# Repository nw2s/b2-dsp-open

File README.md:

# b2-dsp-open
Open sourced hardware and software for the b2-dsp module

## Important Links

[nw2s website](http://nw2s.net)

[nw2s::b2/dsp Confluence](https://nw2sdevices.atlassian.net/wiki/display/NW2SB2DSP)

[nw2s::b2/dsp Jira](https://nw2sdevices.atlassian.net/secure/RapidBoard.jspa?rapidView=2&projectKey=B2)

[nw2s::b2/dsp open source repository](https://github.com/nw2s/b2-dsp-open)

[nw2s on facebook](https://www.facebook.com/nw2smodular/)

## Status

[19-Nov-2016]
A good portion of the hardware design is complete. The panel design is complete and most of the conponent selection is done. The panel board has a little bit of work with regards to spacing and vertical alignment, but is otherwise complete. The mainboard still has a bit of layout work to do to be able to fit everything in with a minimum of interference. There is still a decent amount of work there and prototyping to do. 

Software-wise, I'm primarily working through some issue with the AM57x with the TI Linux kernel and access to the DSP chips via OpenCL. Much of the controller/worker architecture is completed and there is support for a wide array of USB devices. I'm actively building out playable patches for some specific devices. 

[You can see what I'm probably working on in Jira](https://nw2sdevices.atlassian.net/secure/RapidBoard.jspa?rapidView=2&projectKey=B2). Since this is a very small team, it doesn't get updated as often as it shoudld, but it will give you an idea of some of the recent accomplishments and near-future goals. If you aren't familiar with a Kanban board, that is technically how I'm working through the tasks. 

## Licensing
The nw2s::b2/dsp is an open source project. Both the hardware and the software are released as open-source. 

This project builds on many contributors and is open source so that I can give back to the community. Most of them are unknowing contributors, so I've attempted to give credit wherever possible. Code, samples, algorithms, ideas: many of them are gleaned or borrowed, others are built upon. Still others are completely original. 

In the spirit of open-source, I ask that any use of these materials be properly credited and used in accordance with the applicable licenses. If you are not familiar with the common terms of open-source, I ask that you do a little research. Different parts of the project are licensed differently, depending on what it is. 

For the most part, all nw2s::b2/dsp code is licensed with GPL v3. GPL is a restrictive open source license. The gist is that you have access to the code for your own use. You may modify the source code, but you must release the modified source code. GPL also requires that all code that links to the nw2s::b2/dsp code must also be released as open source. This means that if you use any of this code in a project, your project must also be open source. 

With a few exceptions, the documentation and reference materials have been released as Creative Commons Attribution Share Alike. This means that you're free to create new works based on this documentation as long as you give attribution and also share the source material. 

The hardware is open-sourced as well. This is important. There are not many truly open-source hardware projects out there. All of the hardware design is my own and I am sharing it with the community. The hardware is licensed via the CERN OHL v1.2. This means that you are free to modify and even sell derivative works, however all source materials must remain open-sourced as well under the same license. Unfortunately due to the type of project, these are not trivial to source nor trivial to build. Fortunately for you, I don't really make that much money on them.

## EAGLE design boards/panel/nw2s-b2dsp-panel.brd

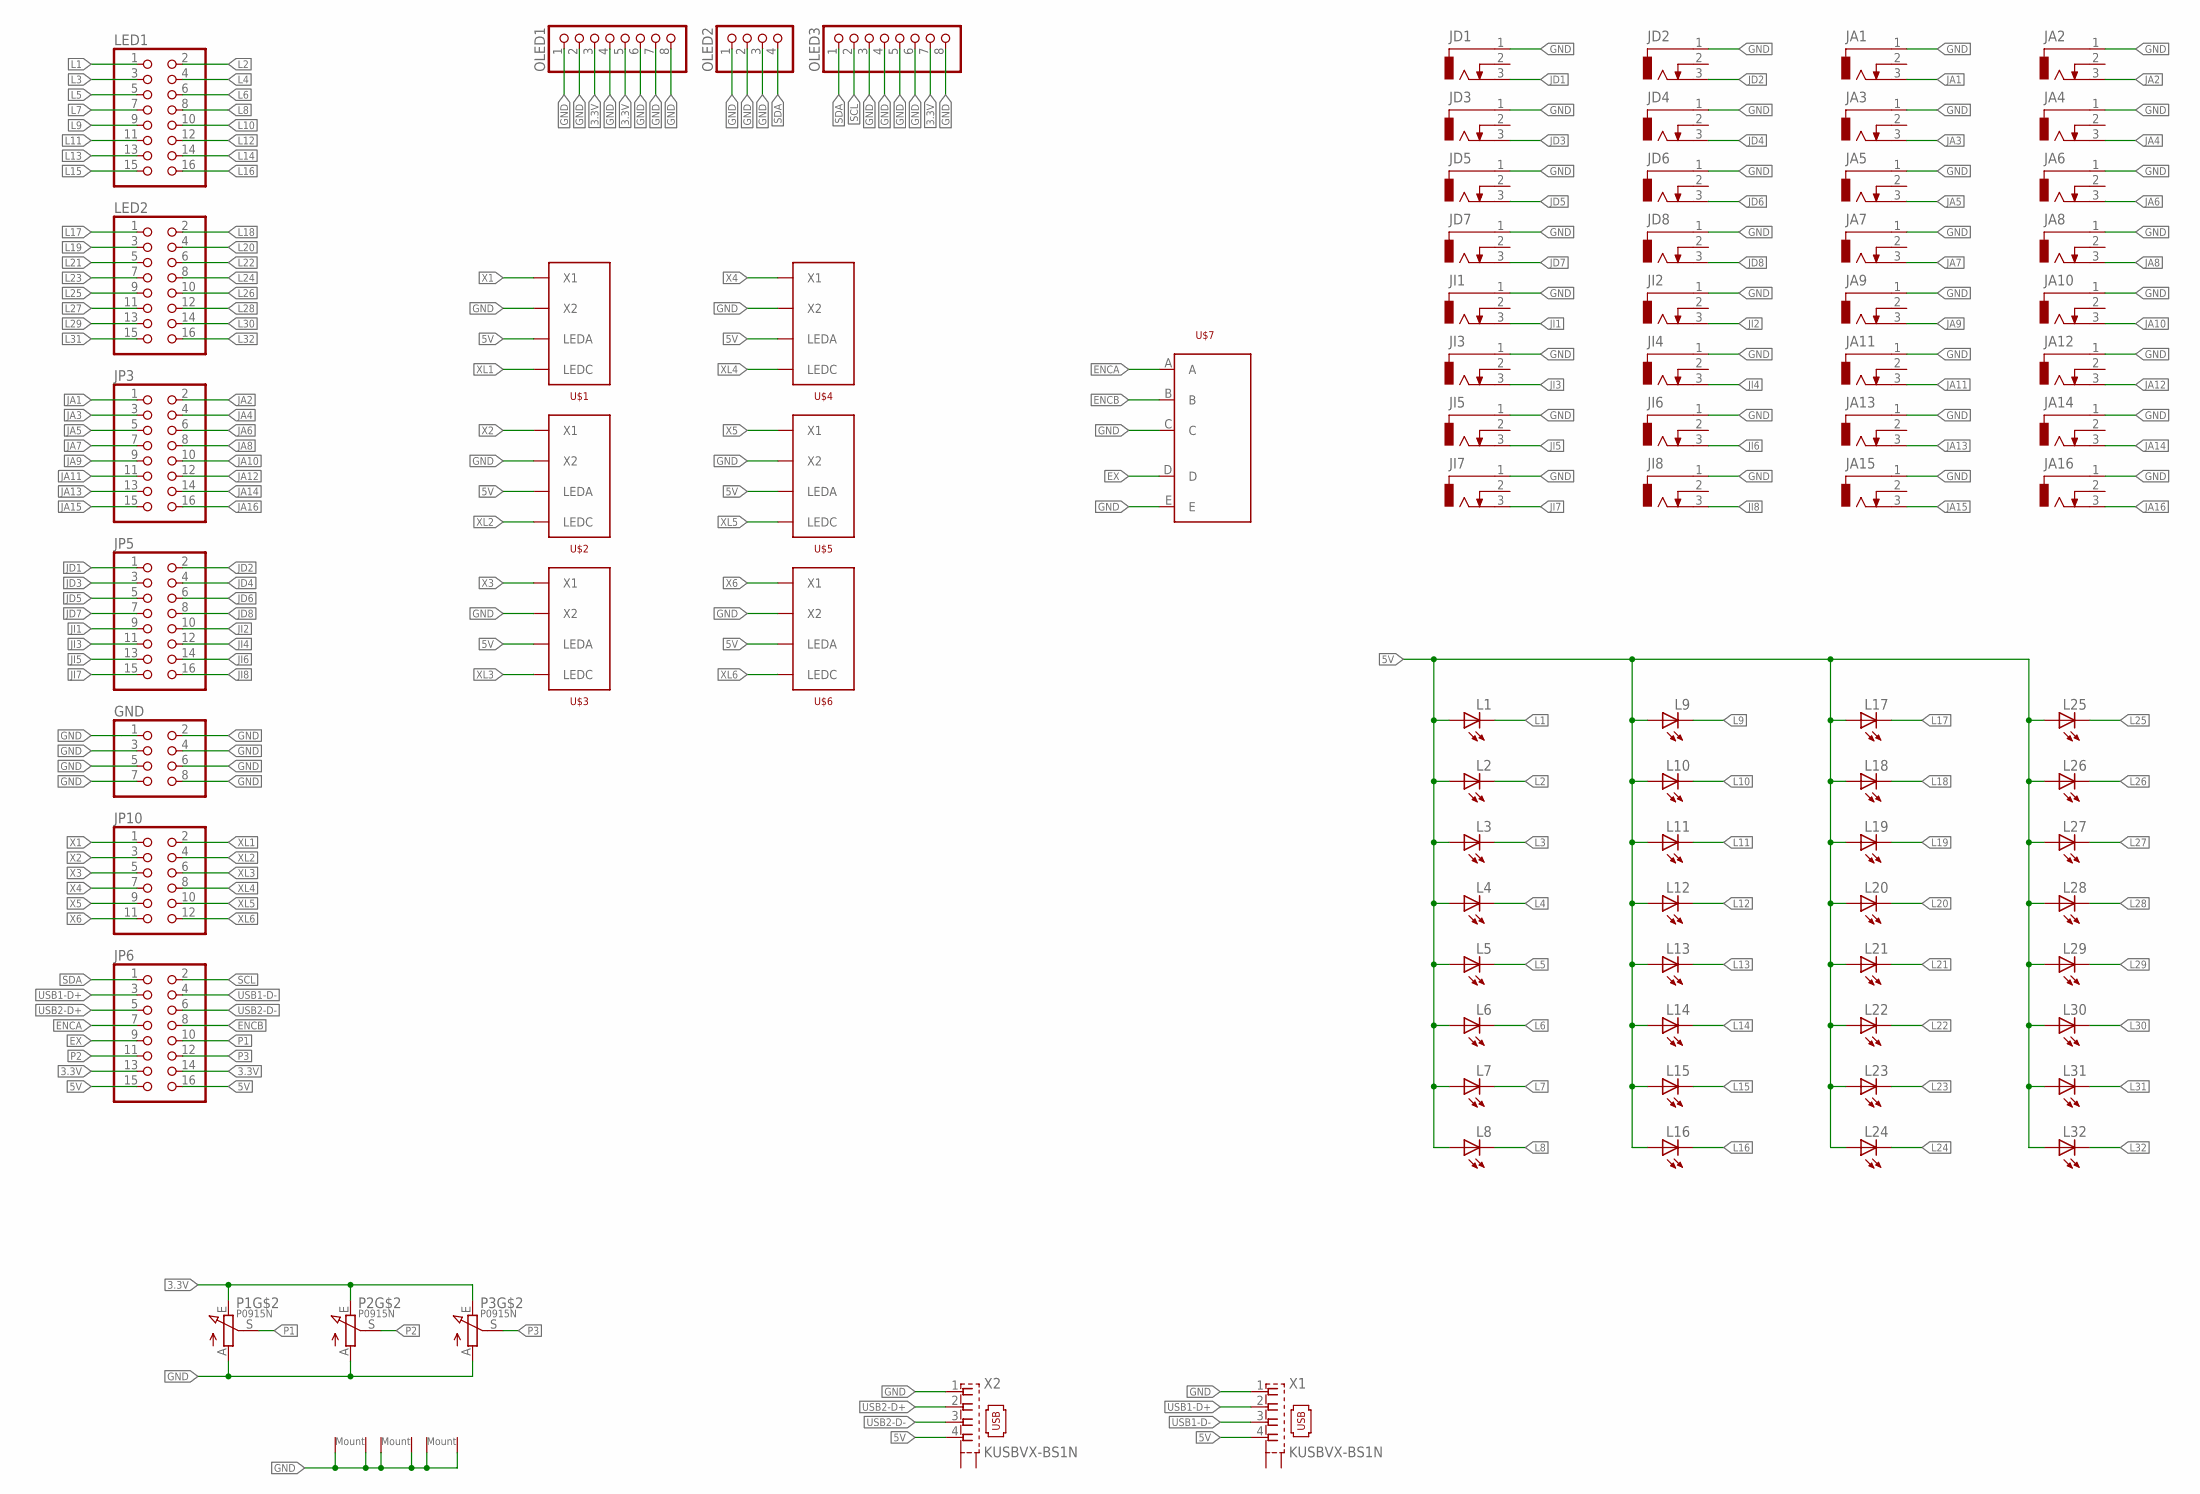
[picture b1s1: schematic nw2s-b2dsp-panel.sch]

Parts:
GND: PINHD-2X4; 2X04
JA1, JA2, JA3, JA4, JA5, JA6, JA7, JA8, JA9, JA10, JA11, JA12, JA13, JA14, JA15, JA16: THONK35A2; THONK35A-2
JD1, JD2, JD3, JD4, JD5, JD6, JD7, JD8: THONK35A2; THONK35A-2
JI1, JI2, JI3, JI4, JI5, JI6, JI7, JI8: THONK35A2; THONK35A-2
JP3, JP5, JP6: PINHD-2X8; 2X08
JP10: PINHD-2X6; 2X06
L1, L2, L3, L4, L5, L6, L7, L8, L9, L10, L11, L12, L13, L14, L15, L16, L17, L18, L19, L20, L21, L22, L23, L24, L25, L26, L27, L28, L29, L30, L31, L32: LED3MM
LED1, LED2: PINHD-2X8; 2X08
OLED1, OLED3: PINHD-1X8; 1X08
OLED2: PINHD-1X4; 1X04
P1, P2, P3: P0915N
U$1, U$2, U$3, U$4, U$5, U$6: MEC5G
U$7: EN11X; EN11
X1, X2: KUSBVX-BS1N

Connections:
3.3V: JP6.13, JP6.14, OLED1.3, OLED1.5, OLED3.7, P1.E, P2.E, P3.E
5V: JP6.15, JP6.16, L1.A, L2.A, L3.A, L4.A, L5.A, L6.A, L7.A, L8.A, L9.A, L10.A, L11.A, L12.A, L13.A, L14.A, L15.A, L16.A, L17.A, L18.A, L19.A, L20.A, L21.A, L22.A, L23.A, L24.A, L25.A, L26.A, L27.A, L28.A, L29.A, L30.A, L31.A, L32.A, U$1.P$4 (LEDA), U$2.P$4 (LEDA), U$3.P$4 (LEDA), U$4.P$4 (LEDA), U$5.P$4 (LEDA), U$6.P$4 (LEDA), X1.4, X2.4
ENCA: JP6.7, U$7.A
ENCB: JP6.8, U$7.B
EX: JP6.9, U$7.D
GND: GND.1, GND.2, GND.3, GND.4, GND.5, GND.6, GND.7, GND.8, JA1.1, JA2.1, JA3.1, JA4.1, JA5.1, JA6.1, JA7.1, JA8.1, JA9.1, JA10.1, JA11.1, JA12.1, JA13.1, JA14.1, JA15.1, JA16.1, JD1.1, JD2.1, JD3.1, JD4.1, JD5.1, JD6.1, JD7.1, JD8.1, JI1.1, JI2.1, JI3.1, JI4.1, JI5.1, JI6.1, JI7.1, JI8.1, OLED1.1, OLED1.2, OLED1.4, OLED1.6, OLED1.7, OLED1.8, OLED2.1, OLED2.2, OLED2.3, OLED3.3, OLED3.4, OLED3.5, OLED3.6, OLED3.8, P1.A, P1.GND@1 (GND), P1.GND@2 (GND), P2.A, P2.GND@1 (GND), P2.GND@2 (GND), P3.A, P3.GND@1 (GND), P3.GND@2 (GND), U$1.P$3 (X2), U$2.P$3 (X2), U$3.P$3 (X2), U$4.P$3 (X2), U$5.P$3 (X2), U$6.P$3 (X2), U$7.C, U$7.E, X1.1, X2.1
JA1: JA1.3, JP3.1
JA2: JA2.3, JP3.2
JA3: JA3.3, JP3.3
JA4: JA4.3, JP3.4
JA5: JA5.3, JP3.5
JA6: JA6.3, JP3.6
JA7: JA7.3, JP3.7
JA8: JA8.3, JP3.8
JA9: JA9.3, JP3.9
JA10: JA10.3, JP3.10
JA11: JA11.3, JP3.11
JA12: JA12.3, JP3.12
JA13: JA13.3, JP3.13
JA14: JA14.3, JP3.14
JA15: JA15.3, JP3.15
JA16: JA16.3, JP3.16
JD1: JD1.3, JP5.1
JD2: JD2.3, JP5.2
JD3: JD3.3, JP5.3
JD4: JD4.3, JP5.4
JD5: JD5.3, JP5.5
JD6: JD6.3, JP5.6
JD7: JD7.3, JP5.7
JD8: JD8.3, JP5.8
JI1: JI1.3, JP5.9
JI2: JI2.3, JP5.10
JI3: JI3.3, JP5.11
JI4: JI4.3, JP5.12
JI5: JI5.3, JP5.13
JI6: JI6.3, JP5.14
JI7: JI7.3, JP5.15
JI8: JI8.3, JP5.16
L1: L1.K (C), LED1.1
L2: L2.K (C), LED1.2
L3: L3.K (C), LED1.3
L4: L4.K (C), LED1.4
L5: L5.K (C), LED1.5
L6: L6.K (C), LED1.6
L7: L7.K (C), LED1.7
L8: L8.K (C), LED1.8
L9: L9.K (C), LED1.9
L10: L10.K (C), LED1.10
L11: L11.K (C), LED1.11
L12: L12.K (C), LED1.12
L13: L13.K (C), LED1.13
L14: L14.K (C), LED1.14
L15: L15.K (C), LED1.15
L16: L16.K (C), LED1.16
L17: L17.K (C), LED2.1
L18: L18.K (C), LED2.2
L19: L19.K (C), LED2.3
L20: L20.K (C), LED2.4
L21: L21.K (C), LED2.5
L22: L22.K (C), LED2.6
L23: L23.K (C), LED2.7
L24: L24.K (C), LED2.8
L25: L25.K (C), LED2.9
L26: L26.K (C), LED2.10
L27: L27.K (C), LED2.11
L28: L28.K (C), LED2.12
L29: L29.K (C), LED2.13
L30: L30.K (C), LED2.14
L31: L31.K (C), LED2.15
L32: L32.K (C), LED2.16
P1: JP6.10, P1.S
P2: JP6.11, P2.S
P3: JP6.12, P3.S
SCL: JP6.2, OLED3.2
SDA: JP6.1, OLED2.4, OLED3.1
USB1-D+: JP6.3, X1.2
USB1-D-: JP6.4, X1.3
USB2-D+: JP6.5, X2.2
USB2-D-: JP6.6, X2.3
X1: JP10.1, U$1.P$2 (X1)
X2: JP10.3, U$2.P$2 (X1)
X3: JP10.5, U$3.P$2 (X1)
X4: JP10.7, U$4.P$2 (X1)
X5: JP10.9, U$5.P$2 (X1)
X6: JP10.11, U$6.P$2 (X1)
XL1: JP10.2, U$1.P$1 (LEDC)
XL2: JP10.4, U$2.P$1 (LEDC)
XL3: JP10.6, U$3.P$1 (LEDC)
XL4: JP10.8, U$4.P$1 (LEDC)
XL5: JP10.10, U$5.P$1 (LEDC)
XL6: JP10.12, U$6.P$1 (LEDC)

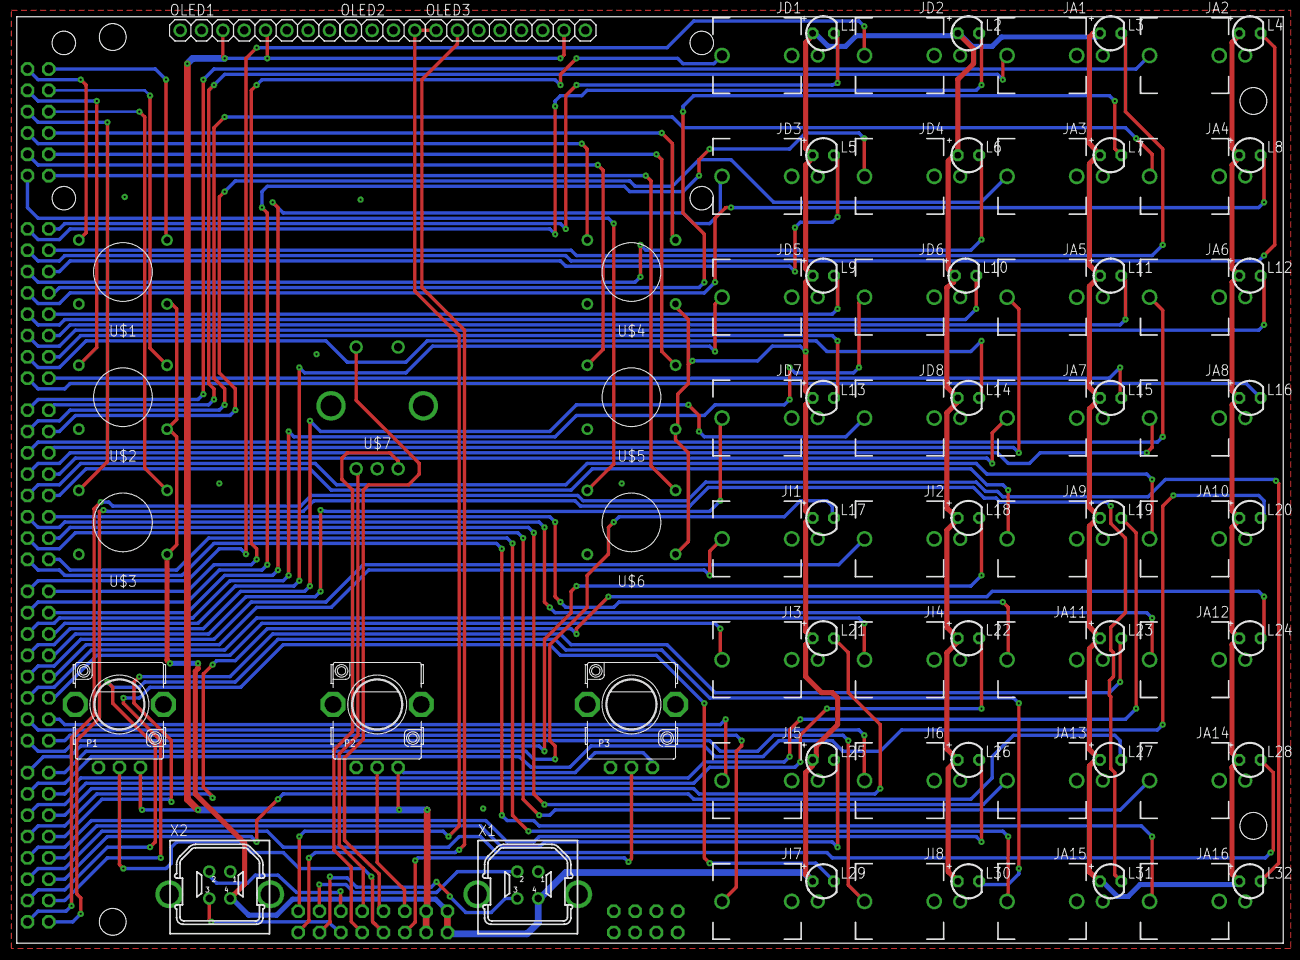
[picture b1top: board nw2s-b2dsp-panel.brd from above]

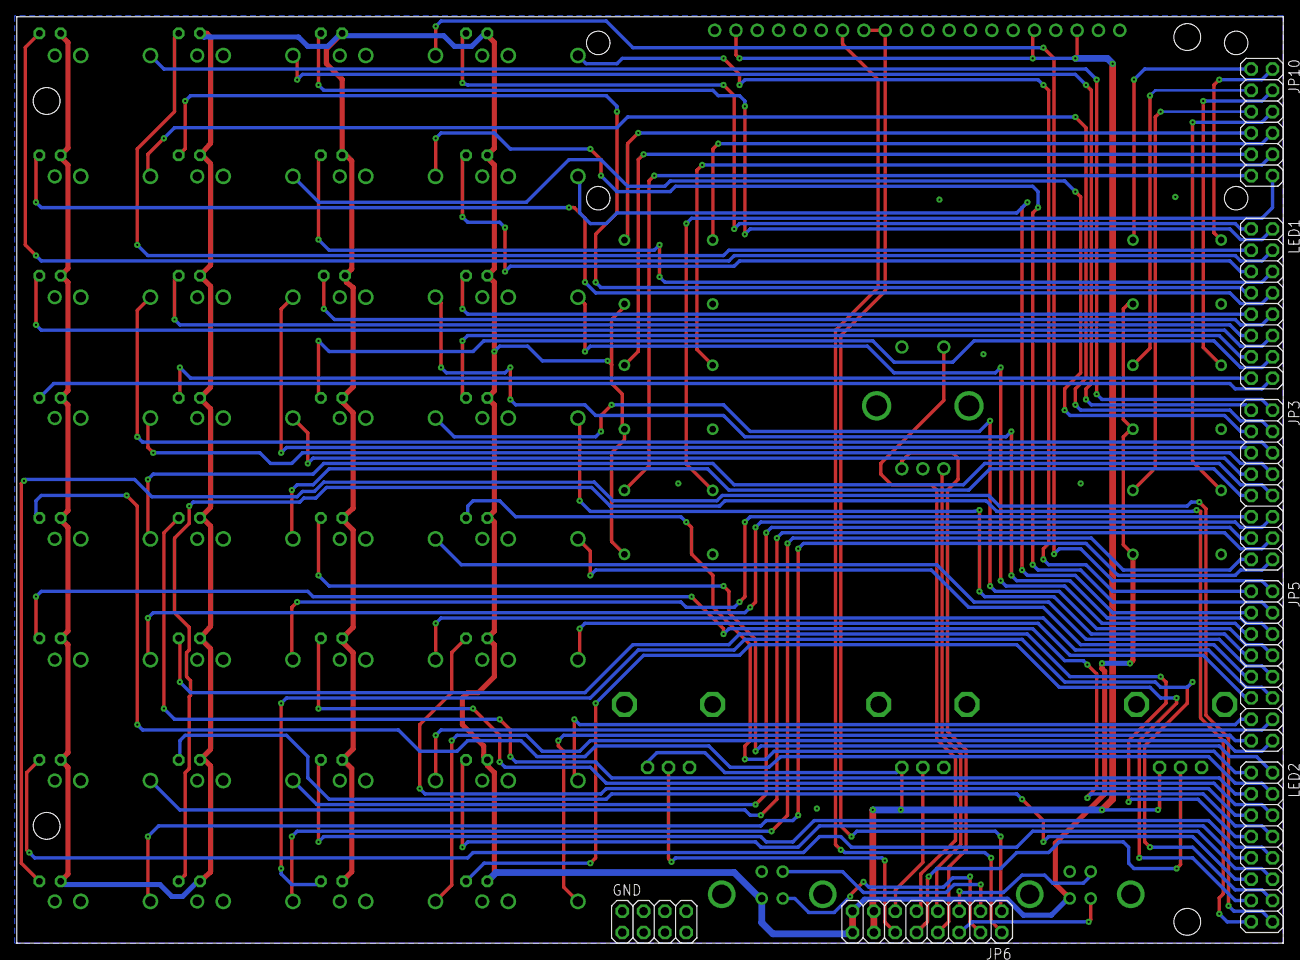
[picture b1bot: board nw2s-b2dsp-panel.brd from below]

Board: 2 copper layers, 150.9 x 110.4 mm, 86 parts (7 on the bottom side), 91 nets.

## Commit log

2016-11-20 licenses
2016-11-20 panel schematics
2016-11-20 panel diagram
